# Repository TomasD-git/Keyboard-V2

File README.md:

# Keyboard-V2
**small, compact keyboard for everyday use.**

## Layout

```
["Esc","1","2","3","4","5","6","7","8","9","0","-","=",{w:2},"Backspace"],
[{w:1.5},"Tab","Q","W","E","R","T","Y","U","I","O","P","[","]",{w:1.5},"\\"],
[{w:1.75},"Caps","A","S","D","F","G","H","J","K","L",";","'",{w:2.25},"Enter"],
[{w:2.25},"Shift","Z","X","C","V","B","N","M",",",".","/",{w:2.75},"Shift"],
[{w:1.25},"Ctrl",{w:1.25},"Win",{w:1.25},"Alt",{w:6.25},"Space",{w:1.25},"Alt",{w:1.25},"Fn",{w:1.25},"Ctrl",{w:1.25},"Esc"]
```

```
        C1  , C2  ,C3 , C4  ,  C5 , C6  ,  C7  , C8  ,  C9 ,  C10 , C11,C12, C13 ,    C14
Row 1 [    ;,    1,  2,    3,    4,    5,     6,    7,    8,     9,   0,  -,    =, backspace]
Row 2 [  tap,    q,  w,    e,    r,    t,     y,    u,    i,     o,   p,  [,    ],    /     ]
Row 3 [ Caps,    a,  s,    d,    f,    g,     h,    j,    k,     l,   ;,  ', Null,   Enter  ]
Row 4 [Shift, Null,  z,    x,    c,    v,     b,    n,    m, comma,   .,  /, Null,  Shift   ]
Row 5 [Ctrl , Win, Alt, Null, Null, Null, Space, Null, Null,  Null, Alt, Fn, Ctrl,  Esc     ]
```

## Features
- Compact 60% layout
- Powered by RPi pico
- Dedicated Fn layer
- Smooth switches
- Stabilizers
- Custom CAD
- Custom PCB

## How It Works
The Keyboard-V2 uses a key matrix to scan all rows and columms. The Fn key enables a secondary layer for additional functionality. The case is 3D printed, with custom PCB and.

<details>
  <summary>Pictures</summary>

</details>

<details>
<summary>BOM</summary>

| Name | Purpose | Quantity | Total Cost (USD) | Link | Distributor |
|------|--------|----------|------------------|------|-------------|
| Stabilizers | Stabilizers are used so keys arent wobly and are in place | 1 | 8.00 | https://www.aliexpress.com/item/1005006528731543.html | Aliexpress |
| PCB | On the PCB are all components | 1 | 44.11 | https://jlcpcb.com | JlcPCB |
| Key switch | the actual switch u press to get a signal | 1 | 21.00 | https://www.aliexpress.com/item/1005007459638140.html | Aliexpress |
| Diodes | prevents ghosting | 1 | 3.00 | https://www.aliexpress.com/item/1005007160563285.html | Aliexpress |
| RPi Pico | Brain of the whole keyboard | 1 | 4.30 | https://www.aliexpress.com/item/1005008714908011.html | Aliexpress |
| M2 screws | Small set of M2 screws to hold the keyboard in place | 1 | 7.40 | https://www.aliexpress.com/item/1005006827233117.html | Aliexpress |
| M2xL3xOD3.2, Heatset inserts | Will hold the keyboard together with screws | 1 | 5.00 | https://www.aliexpress.com/item/1005006838108683.html | Aliexpress |
| Keycaps | are on switches | 1 | 15.00 | https://www.aliexpress.com/item/1005007360831985.html | Aliexpress |

</details>

<details>
  <summary>License</summary>

## MIT License

**Copyright (c) 2026 TomasD-git**

Permission is hereby granted, free of charge, to any person obtaining a copy
of this software and associated documentation files (the "Software"), to deal
in the Software without restriction, including without limitation the rights
to use, copy, modify, merge, publish, distribute, sublicense, and/or sell
copies of the Software, and to permit persons to whom the Software is
furnished to do so, subject to the following conditions:

The above copyright notice and this permission notice shall be included in all
copies or substantial portions of the Software.

THE SOFTWARE IS PROVIDED "AS IS", WITHOUT WARRANTY OF ANY KIND, EXPRESS OR
IMPLIED, INCLUDING BUT NOT LIMITED TO THE WARRANTIES OF MERCHANTABILITY,
FITNESS FOR A PARTICULAR PURPOSE AND NONINFRINGEMENT. IN NO EVENT SHALL THE
AUTHORS OR COPYRIGHT HOLDERS BE LIABLE FOR ANY CLAIM, DAMAGES OR OTHER
LIABILITY, WHETHER IN AN ACTION OF CONTRACT, TORT OR OTHERWISE, ARISING FROM,
OUT OF OR IN CONNECTION WITH THE SOFTWARE OR THE USE OR OTHER DEALINGS IN THE
SOFTWARE.

</details>

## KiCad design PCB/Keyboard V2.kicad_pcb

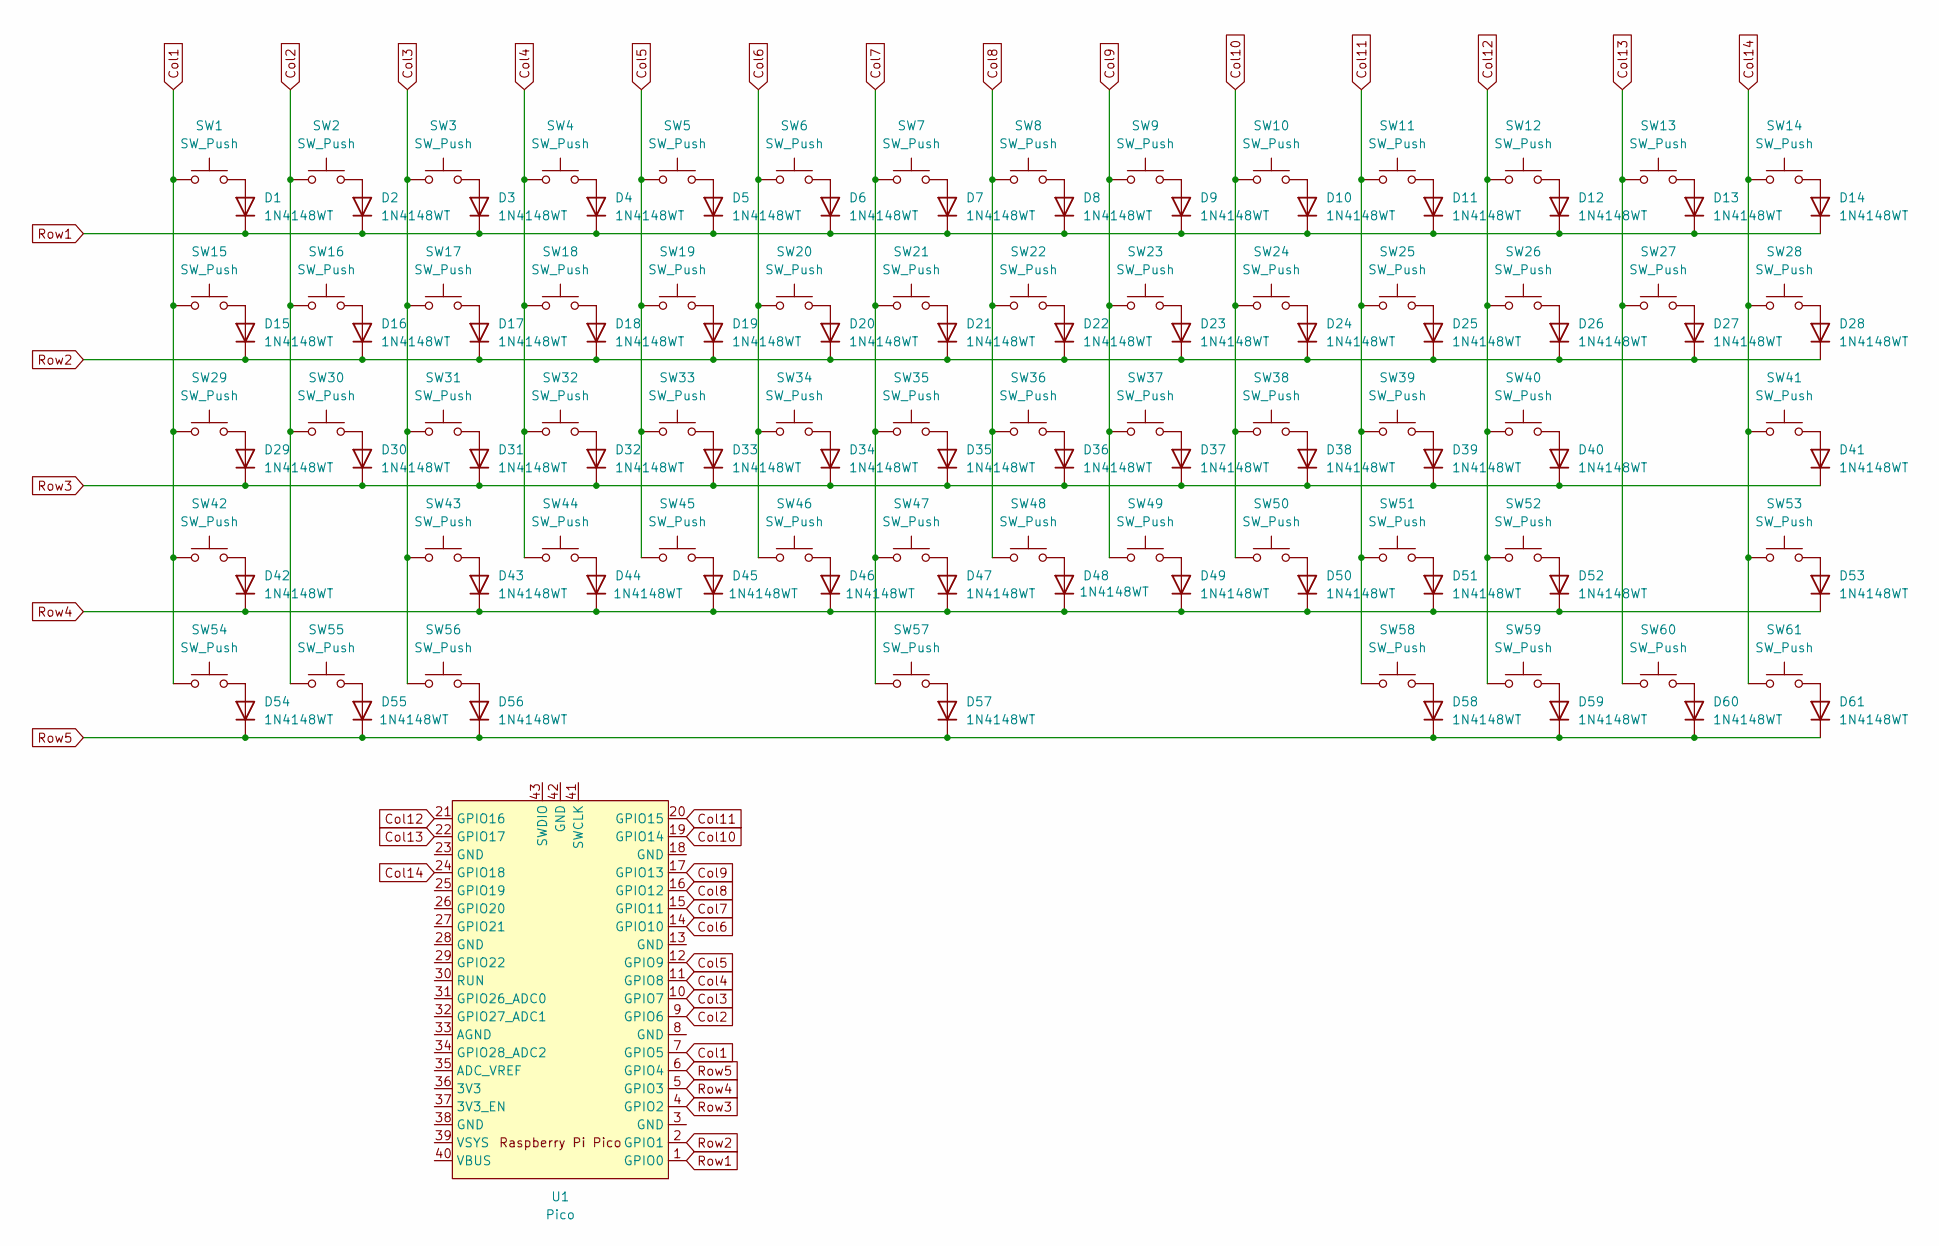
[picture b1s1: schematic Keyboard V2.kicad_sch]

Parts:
D1, D2, D3, D4, D5, D6, D7, D8, D9, D10, D11, D12, D13, D14, D15, D16, D17, D18, D19, D20, D21, D22, D23, D24, D25, D26, D27, D28, D29, D30, D31, D32, D33, D34, D35, D36, D37, D38, D39, D40, D41, D42, D43, D44, D45, D46, D47, D48, D49, D50, D51, D52, D53, D54, D55, D56, D57, D58, D59, D60, D61: 1N4148WT; D_SOD-123
SW1, SW2, SW3, SW4, SW5, SW6, SW7, SW8, SW9, SW10, SW11, SW12, SW13, SW16, SW17, SW18, SW19, SW20, SW21, SW22, SW23, SW24, SW25, SW26, SW27, SW30, SW31, SW32, SW33, SW34, SW35, SW36, SW37, SW38, SW39, SW40, SW43, SW44, SW45, SW46, SW47, SW48, SW49, SW50, SW51, SW52: SW_Push; SW_Cherry_MX_PCB_1.00u
SW14: SW_Push; SW_Cherry_MX_2.00u_PCB
SW15, SW28: SW_Push; SW_Cherry_MX_PCB_1.50u
SW29: SW_Push; SW_Cherry_MX_PCB_1.75u
SW41, SW42: SW_Push; SW_Cherry_MX_2.25u_PCB
SW53: SW_Push; SW_Cherry_MX_2.75u_PCB
SW54, SW55, SW56, SW58, SW59, SW60, SW61: SW_Push; SW_Cherry_MX_PCB_1.25u
SW57: SW_Push; SW_Cherry_MX_6.25u_PCB
U1: Pico; RPi_Pico_SMD_TH

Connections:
Col1: SW1.1, SW15.1, SW29.1, SW42.1, SW54.1, U1.7 (GPIO5)
Col2: SW2.1, SW16.1, SW30.1, SW55.1, U1.9 (GPIO6)
Col3: SW3.1, SW17.1, SW31.1, SW43.1, SW56.1, U1.10 (GPIO7)
Col4: SW4.1, SW18.1, SW32.1, SW44.1, U1.11 (GPIO8)
Col5: SW5.1, SW19.1, SW33.1, SW45.1, U1.12 (GPIO9)
Col6: SW6.1, SW20.1, SW34.1, SW46.1, U1.14 (GPIO10)
Col7: SW7.1, SW21.1, SW35.1, SW47.1, SW57.1, U1.15 (GPIO11)
Col8: SW8.1, SW22.1, SW36.1, SW48.1, U1.16 (GPIO12)
Col9: SW9.1, SW23.1, SW37.1, SW49.1, U1.17 (GPIO13)
Col10: SW10.1, SW24.1, SW38.1, SW50.1, U1.19 (GPIO14)
Col11: SW11.1, SW25.1, SW39.1, SW51.1, SW58.1, U1.20 (GPIO15)
Col12: SW12.1, SW26.1, SW40.1, SW52.1, SW59.1, U1.21 (GPIO16)
Col13: SW13.1, SW27.1, SW60.1, U1.22 (GPIO17)
Col14: SW14.1, SW28.1, SW41.1, SW53.1, SW61.1, U1.24 (GPIO18)
unnamed: D1.2 (A), SW1.2
unnamed: D2.2 (A), SW2.2
unnamed: D3.2 (A), SW3.2
unnamed: D4.2 (A), SW4.2
unnamed: D5.2 (A), SW5.2
unnamed: D6.2 (A), SW6.2
unnamed: D7.2 (A), SW7.2
unnamed: D8.2 (A), SW8.2
unnamed: D9.2 (A), SW9.2
unnamed: D10.2 (A), SW10.2
unnamed: D11.2 (A), SW11.2
unnamed: D12.2 (A), SW12.2
unnamed: D13.2 (A), SW13.2
unnamed: D14.2 (A), SW14.2
unnamed: D15.2 (A), SW15.2
unnamed: D16.2 (A), SW16.2
unnamed: D17.2 (A), SW17.2
unnamed: D18.2 (A), SW18.2
unnamed: D19.2 (A), SW19.2
unnamed: D20.2 (A), SW20.2
unnamed: D21.2 (A), SW21.2
unnamed: D22.2 (A), SW22.2
unnamed: D23.2 (A), SW23.2
unnamed: D24.2 (A), SW24.2
unnamed: D25.2 (A), SW25.2
unnamed: D26.2 (A), SW26.2
unnamed: D27.2 (A), SW27.2
unnamed: D28.2 (A), SW28.2
unnamed: D29.2 (A), SW29.2
unnamed: D30.2 (A), SW30.2
unnamed: D31.2 (A), SW31.2
unnamed: D32.2 (A), SW32.2
unnamed: D33.2 (A), SW33.2
unnamed: D34.2 (A), SW34.2
unnamed: D35.2 (A), SW35.2
unnamed: D36.2 (A), SW36.2
unnamed: D37.2 (A), SW37.2
unnamed: D38.2 (A), SW38.2
unnamed: D39.2 (A), SW39.2
unnamed: D40.2 (A), SW40.2
unnamed: D41.2 (A), SW41.2
unnamed: D42.2 (A), SW42.2
unnamed: D43.2 (A), SW43.2
unnamed: D44.2 (A), SW44.2
unnamed: D45.2 (A), SW45.2
unnamed: D46.2 (A), SW46.2
unnamed: D47.2 (A), SW47.2
unnamed: D48.2 (A), SW48.2
unnamed: D49.2 (A), SW49.2
unnamed: D50.2 (A), SW50.2
unnamed: D51.2 (A), SW51.2
unnamed: D52.2 (A), SW52.2
unnamed: D53.2 (A), SW53.2
unnamed: D54.2 (A), SW54.2
unnamed: D55.2 (A), SW55.2
unnamed: D56.2 (A), SW56.2
unnamed: D57.2 (A), SW57.2
unnamed: D58.2 (A), SW58.2
unnamed: D59.2 (A), SW59.2
unnamed: D60.2 (A), SW60.2
unnamed: D61.2 (A), SW61.2
Row1: D1.1 (K), D2.1 (K), D3.1 (K), D4.1 (K), D5.1 (K), D6.1 (K), D7.1 (K), D8.1 (K), D9.1 (K), D10.1 (K), D11.1 (K), D12.1 (K), D13.1 (K), D14.1 (K), U1.1 (GPIO0)
Row2: D15.1 (K), D16.1 (K), D17.1 (K), D18.1 (K), D19.1 (K), D20.1 (K), D21.1 (K), D22.1 (K), D23.1 (K), D24.1 (K), D25.1 (K), D26.1 (K), D27.1 (K), D28.1 (K), U1.2 (GPIO1)
Row3: D29.1 (K), D30.1 (K), D31.1 (K), D32.1 (K), D33.1 (K), D34.1 (K), D35.1 (K), D36.1 (K), D37.1 (K), D38.1 (K), D39.1 (K), D40.1 (K), D41.1 (K), U1.4 (GPIO2)
Row4: D42.1 (K), D43.1 (K), D44.1 (K), D45.1 (K), D46.1 (K), D47.1 (K), D48.1 (K), D49.1 (K), D50.1 (K), D51.1 (K), D52.1 (K), D53.1 (K), U1.5 (GPIO3)
Row5: D54.1 (K), D55.1 (K), D56.1 (K), D57.1 (K), D58.1 (K), D59.1 (K), D60.1 (K), D61.1 (K), U1.6 (GPIO4)

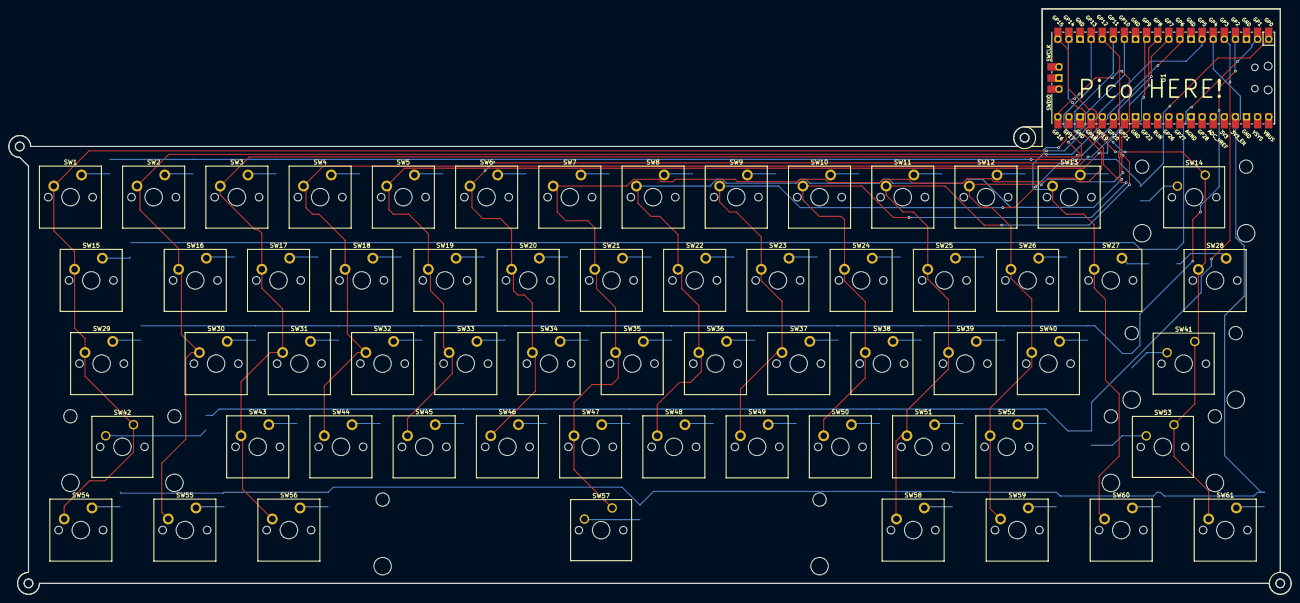
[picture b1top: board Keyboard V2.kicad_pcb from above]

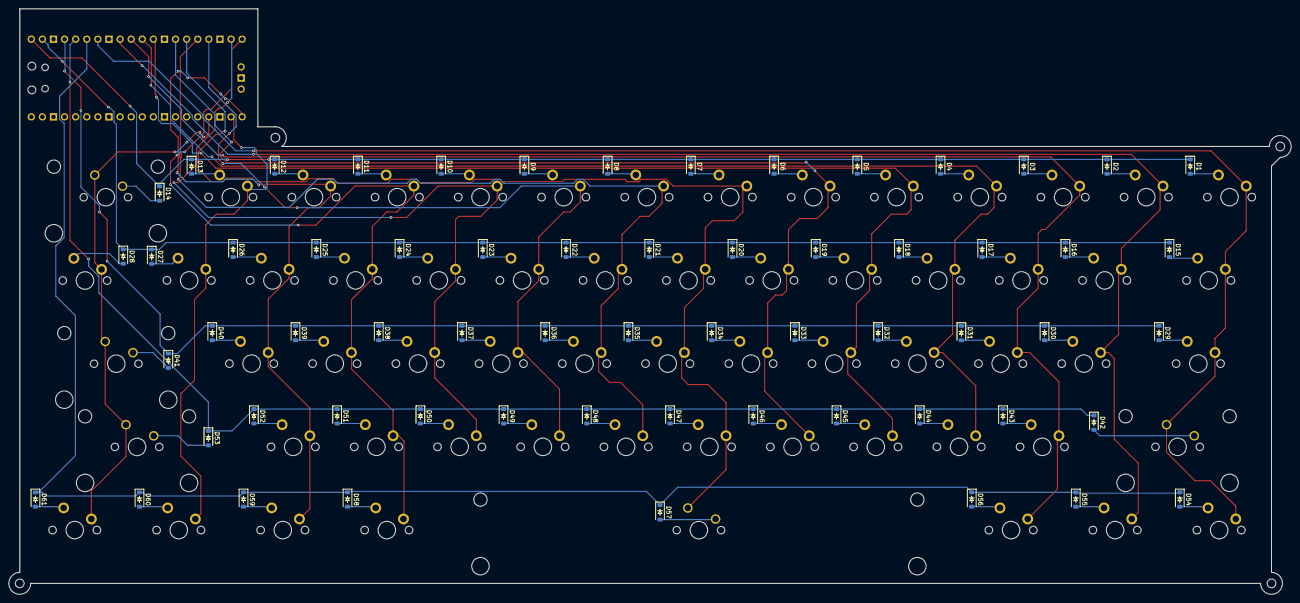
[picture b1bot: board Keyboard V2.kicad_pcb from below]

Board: 2 copper layers, 293.5 x 134.0 mm, 123 parts (61 on the bottom side), 80 nets.

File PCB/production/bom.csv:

Designator,Footprint,Quantity,Value,LCSC Part #
"D1, D10, D11, D12, D13, D14, D15, D16, D17, D18, D19, D2, D20, D21, D22, D23, D24, D25, D26, D27, D28, D29, D3, D30, D31, D32, D33, D34, D35, D36, D37, D38, D39, D4, D40, D41, D42, D43, D44, D45, D46, D47, D48, D49, D5, D50, D51, D52, D53, D54, D55, D56, D57, D58, D59, D6, D60, D61, D7, D8, D9",D_SOD-123,61,1N4148WT,
"SW1, SW10, SW11, SW12, SW13, SW16, SW17, SW18, SW19, SW2, SW20, SW21, SW22, SW23, SW24, SW25, SW26, SW27, SW3, SW30, SW31, SW32, SW33, SW34, SW35, SW36, SW37, SW38, SW39, SW4, SW40, SW43, SW44, SW45, SW46, SW47, SW48, SW49, SW5, SW50, SW51, SW52, SW6, SW7, SW8, SW9",SW_Cherry_MX_PCB_1.00u,46,SW_Push,
SW14,SW_Cherry_MX_2.00u_PCB,1,SW_Push,
"SW15, SW28",SW_Cherry_MX_PCB_1.50u,2,SW_Push,
SW29,SW_Cherry_MX_PCB_1.75u,1,SW_Push,
"SW41, SW42",SW_Cherry_MX_2.25u_PCB,2,SW_Push,
SW53,SW_Cherry_MX_2.75u_PCB,1,SW_Push,
"SW54, SW55, SW56, SW58, SW59, SW60, SW61",SW_Cherry_MX_PCB_1.25u,7,SW_Push,
SW57,SW_Cherry_MX_6.25u_PCB,1,SW_Push,
U1,RPi_Pico_SMD_TH,1,Pico,

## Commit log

2026-04-09 Enhance README formatting and add key layout
    Formatted the README with bold text and added key layout example.
2026-04-10 Update links in README for keycaps and RPI pico
2026-04-10 Add link for M2xL3xOD3.2 heatset inserts
2026-04-11 Add keyboard layout and keycap links to README
2026-04-11 Update README with firmware setup instructions
    Added detailed setup instructions for flashing CircuitPython and installing KMK on Raspberry Pi Pico.
2026-04-11 Fix typo in README setup section
2026-04-11 added code.py
2026-04-11 Add README.md for KiCad files
2026-04-11 added PCB files
2026-04-11 Add README.md for CAD files
2026-04-11 added CAD files
2026-04-11 Revise README with layout and features details
    Updated README to enhance layout and features section.
2026-04-11 Create LICENSE
2026-04-11 Fix formatting of MIT License section in README
2026-04-11 added BOM
2026-04-11 Enhance README with images and formatting
2026-04-11 Update README with feature enhancements and corrections
    Corrected capitalization and added new features to the README.
2026-04-24 added gbr file
2026-04-24 Add BOM section to README
    Added a BOM section detailing components, their purposes, quantities, costs, and links.
2026-04-27 added bottom CAD file
2026-04-27 added pcb picture
